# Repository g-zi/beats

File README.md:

# BEATS
## Beat Couter, MIDI controller and DMX light controller in one

A small box that is connected to the computer via USB and shows the beat as a clock and digits so that can be mixed in the beat. It can be used as a MIDI and DMX controller and can control a lighting system in the beat.

The Beat Counter knows 3 operating modes:

- MIDI (drum pad, beat clock and metronome)
- Scanners (and moving heads with up to 8 scanners with 8 channels or 4 scanners with up to 16 channels)
- COB (Pixbar and Pattern)

Can operate with anything that sends/receives MIDI commands: Ableton Live, Serato, Traktor …

Beat length adjustable, inclined beats such as 9 are also adjustable.
The key matrix is pressure-sensitive and illuminated with RGB LEDs. A milky silicone pad is attached to the key matrix.
There are two illuminated encoders that are used to set the lighting system and can also send MIDI signals.
Reads and writes MIDI signals via USB and DIN socket.
Outputs DMX control signals for light control for COB bars, 8x8 COB arrays and scanners / moving heads. Up to 8 scanners / moving heads can be controlled at the same time.
SD card slot accessible from the rear.
The housing is designed with OpenSCAD and is printed with 3D printers (Form3 or FDM)
The current version uses a Teensy 3.6, the next version will have a Teensy 4.1 (600Mhz).
The board is two-sided and created with Eagle.

Here some videos: 
- Controlling scanners / moving heads: https://www.youtube.com/watch?v=9kyjajE7mRk
- Animation of the circuit board: https://www.youtube.com/watch?v=K_6d6vQXQpI 
- Inner workings with a few functions: https://www.youtube.com/watch?v=Ms0J2bLOR1w 
- 4 x Showtec Pixel Square 16 COB (old version): https://www.youtube.com/watch?v=BX3hZSje4Ws
- Also works with bars (old version): https://www.youtube.com/watch?v=ibh8aw3B2aw
- MIDI Beat Counter Setup and Menues Part 1: https://www.youtube.com/watch?v=dCm0thBqy6s
- MIDI Beat Counter Setup and Menues Part 2: https://www.youtube.com/watch?v=OodJnmjo3fk

In MIDI mode, the key matrix is used as pressure-sensitive pads for e.g. Ableton Live. All buttons send MIDI commands. The two encoders send MIDI commands for buttons and each can be switched between 3 settings. MIDI channel and address can be set.

The scanner mode is used to control up to 8 scanners or moving heads with 8 channels or 4 scanners with up to 16 channels. All settings such as pan, tilt, color, strobe etc. can be set individually for each scanner and up to 32 settings can be saved by now.

In movement mode there are 9 movement patterns such as Left-Right, Circle, Swing etc. which the scanner let move to the rhythm of the music. The movement path and speed can be selected, in beat in steps and free run mode.

The COB mode is for COB-LED walls, until now for a matrix of 8x8 COBs. A counting pattern can be set or programmed patterns can be send out. The patterns run to the beat of the music, foreground and background brightness can be adjusted. Lightbulbs are simulated, slowly decay.

The housing is designed to be as stable as possible. On the underside there are bars under the key matrix so that nothing can bend or break even with firm pressure. The two screws for the circuit board are in the immediate vicinity of the encoder, even here nothing can be broken by applying too much pressure to the encoder. An M8 nut will also be integrated into the housing on the underside so that the device can also be screwed on. The size of the Beat Counter is kept compact and can therefore be mounted within sight.

## Further development:

The USB host port can be used to connect external devices, keyboard, drum pads etc. (Korg, Akai) https://www.pjrc.com/wp-content/uploads/2020/05/teensy41_usbhost3.jpg https://forum.pjrc.com/teensy41_usbhost2.jpg

Explanation to DMX: https://en.wikipedia.org/wiki/DMX512#RJ-45_pinout

In the current device I am using a Teensy 3.6. I am developing a circuit board for the Teensy 4.1. Teensy 4.1: https://www.pjrc.com/store/teensy41.html

Instead of the MIDI-DIN socket, an RJ45 socket will be installed: Ethernet can be used to beat-link CDJs such as beat-link-trigger or for Art-Net

Art-Net: https://artisticlicence.com/WebSiteMaster/User%20Guides/art-net.pdf

Conversion of the pattern for the COB-LED walls to the SD card and writing the program for generating the pattern, then larger output than 8x8 are possible.

Teensy 4.1 can use S/PDIF and can be later used for sound analysis, Fourier transformation and as an effects device: https://en.wikipedia.org/wiki/S/PDIF

The displays are also available in round. This display can be exchanged 1: 1 (same driver ST7789): 250nits: http://www.panelook.com/TVT0128A-I-IPS-1-28-Inch-240x240-Round-TFT-LCD-Circular-Display-Module-For-VR-detail_71679.html 400nits: http://www.panelook.com/TVT0128C-I-IPS-1-28-Inch-240x240-Round-TFT-LCD-Circular-Display-Module-For-VR-detail_98507.html or as OLED with 400x400 resolution, but are quite expensive and probably too slow: https://www.ebay.de/itm/Real-AMOLED-Display-1-39-inch-400-400-Round-Circle-Circular-OLED-LCD-Module/192716558403?var=492858328484

An LED strip control can also be installed, the neopixels are already controlled like this: https://www.ebay.de/itm/WS2812B-LED-Streifen-Strip-5M-WS2812-RGB-Leiste-Licht-5050-SMD-Adressbaren-DC5V/222192610445?hash=item33bbb62c8dⓂ️m48DHbcLw8Ppkncw-fkDSGA

Something else interesting could easily be integrated: https://github.com/saikoLED/TeensyLED

If someone is interrested to build it, I still have some PCB's and can send for 10 Euros each plus shipping costs. For further questions send email to g.zi@gmx.de

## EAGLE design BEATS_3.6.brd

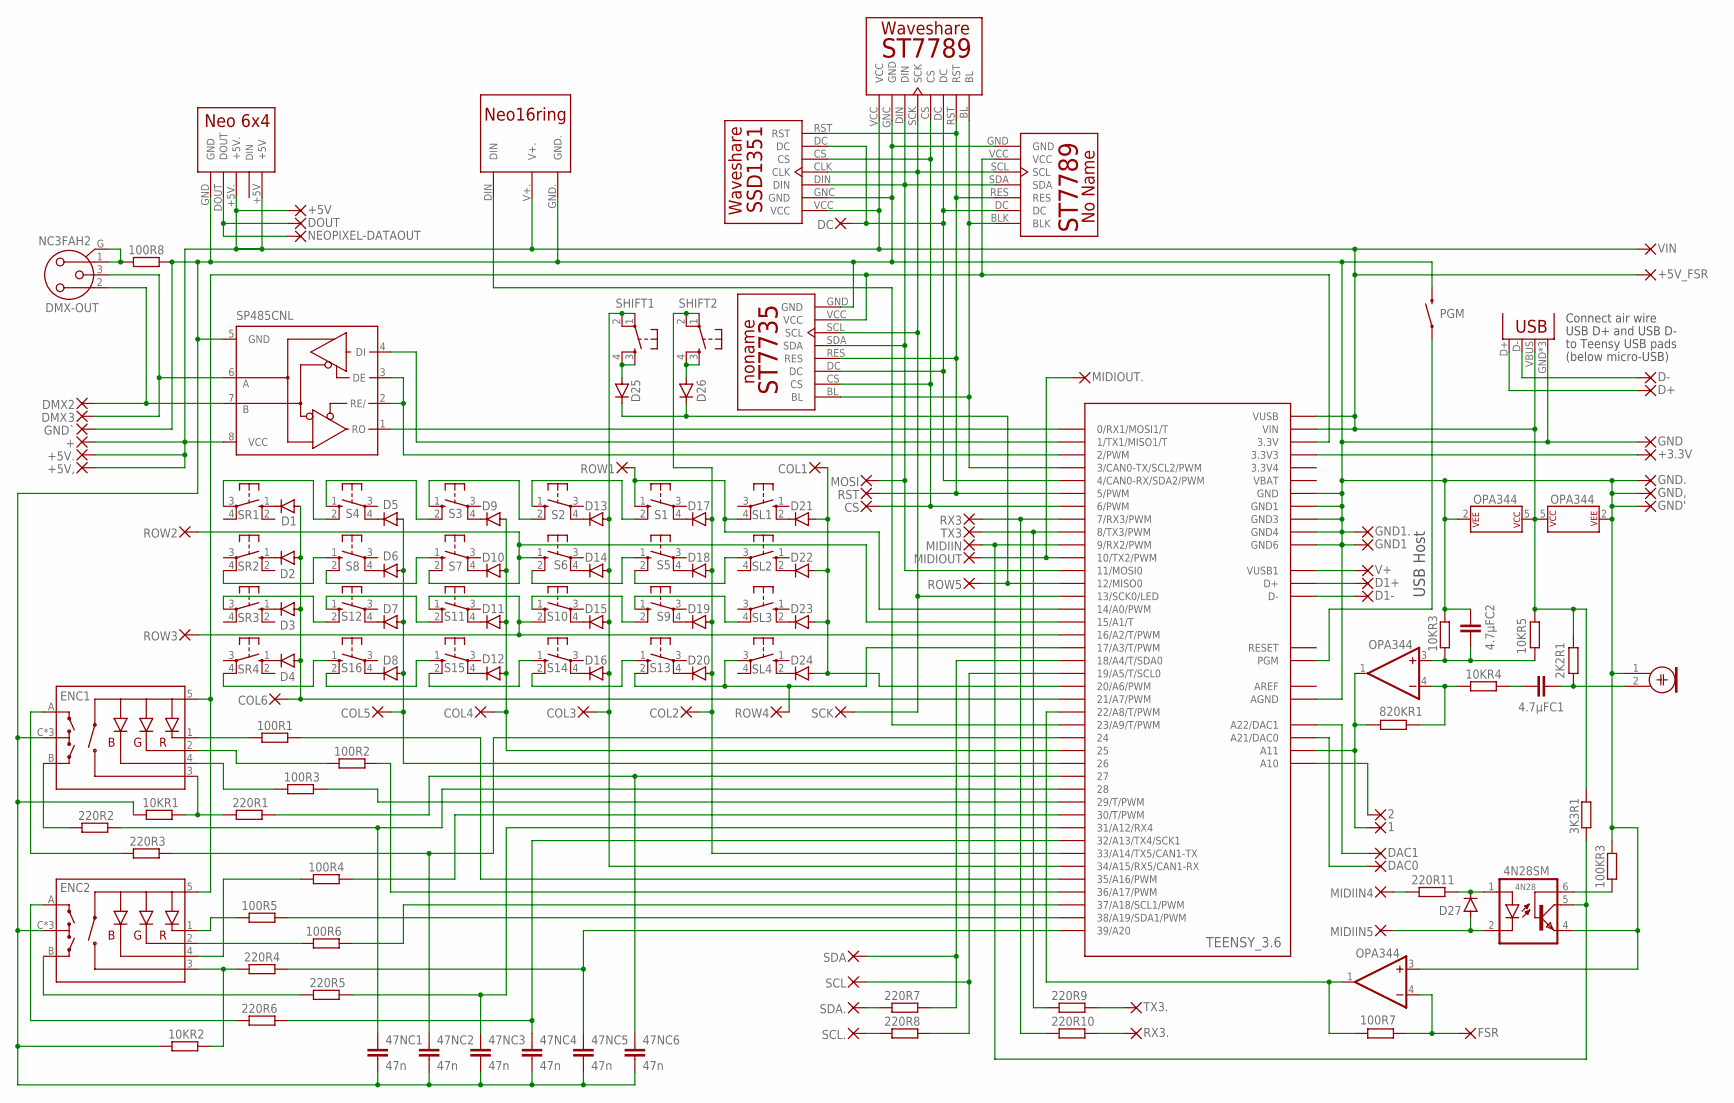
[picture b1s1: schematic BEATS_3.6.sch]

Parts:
1, 2, 3: 1,6/0,8
2K2R1: 2K2; R0603
3K3R1: 3k3; R0603
4.7µFC1, 4.7µFC2: 4.7µF; C1210
4N28: 4N28SM; DIL6-SMD
10KR1, 10KR2: 10k; R0603
10KR3, 10KR4, 10KR5: 10K; R0603
47NC1, 47NC2, 47NC3, 47NC4, 47NC5, 47NC6: 47n; C0603
100KR3: 100k; R0603
100R1, 100R2, 100R3, 100R4, 100R5, 100R6, 100R8, 220R1, 220R2, 220R3, 220R4, 220R5, 220R6, 220R7, 220R8, 220R9, 220R10, 220R11: 220R; R0603
100R7: 100R; R0603
820KR1: 820K; R0603
+, +5V, +5V,, +5V., +5V_FSR: 1,6/0,8
+3.3V: +3.3v; 1,6/0,8
COL1, COL2, COL3, COL4, COL5, COL6: 1,6/0,8
CS: 1,6/0,8
D1, D2, D3, D4, D5, D6, D7, D8, D9, D10, D11, D12, D13, D14, D15, D16, D17, D18, D19, D20, D21, D22, D23, D24, D25, D26, D27: 1N4148DO34-5; DO34-5
D1+, D1-: 1,6/0,8
D+: 1,6/0,8
D-: 1,6/0,8
DAC0, DAC1: 1,6/0,8
DC: 1,6/0,8
DMX2: 1,6/0,8
DMX-OUT: NC3FAH2
DOUT: 1,6/0,8
ENC1, ENC2: ENCODER-RGB-SWITCHENCODER_LED_3_LONG; ENCODER_LED_3_LONG
FSR: 1,6/0,8
GND, GND1, GND1., GND.: 1,6/0,8
GND': 1,6/0,8
GND,: 1,6/0,8
GND`: 1,6/0,8
MIC: ELECTRET_MICROPHON-F6035AP; F6035AP
MIDIIN, MIDIIN4, MIDIIN5: 1,6/0,8
MIDIOUT, MIDIOUT.: 1,6/0,8
MOSI: 1,6/0,8
NEOPIXEL-DATAOUT: 1,6/0,8
OPA348,, OPA348.: OPA344; SOT23-5
PGM: MOMENTARY-SWITCH-SPST-SMD-4.6X2.8MM; TACTILE_SWITCH_SMD_4.6X2.8MM
ROW1, ROW2, ROW3, ROW4, ROW5: 1,6/0,8
RST: 1,6/0,8
RX3, RX3.: 1,6/0,8
S1, S2, S3, S4, S5, S6, S7, S8, S9, S10, S11, S12, S13, S14, S15, S16: 10-XXLONG; B3F-10XX
SCK: 1,6/0,8
SCL, SCL.: 1,6/0,8
SDA, SDA.: 1,6/0,8
SHIFT1, SHIFT2: MOMENTARY-SWITCH-SPST-2-SMD-5.2MM; TACTILE_SWITCH_SMD_5.2MM
SL1, SL2, SL3, SL4: 10-XXIN; B3F-10XX1
SP485CNL: MAX3468CSA; SO08
SR1, SR2, SR3, SR4: 10-XXIN; B3F-10XX1
TEENSY_3.6: TEENSY_3.6_ALL_PINS
TX3, TX3.: 1,6/0,8
U$1: WS_1.3"240X240_3.3V
U$2: WS_1.5"128X128_OLEDOLED; WS_1.5"128X128_OLED
U$3: WS_1.3"240X240ROUND; WS_1.3"240X240_ROUND
U$4: NEO16RING
U$5: WS_1.44"128X128WS_1.44"128X128; WS_1.44"128X128
U$7: NEOPIXEL_6X4
USB-B: USB-B-H
V+: 1,6/0,8
VIN: +3.3v; 1,6/0,8

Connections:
3.3V: +3.3V.1, TEENSY_3.6.3.3V3
3.3V4: TEENSY_3.6.3.3V4
3V3: ENC1.5 (+), ENC2.5 (+), TEENSY_3.6.3.3V, U$1.VCC, U$5.VCC
AIN1: 1.1, 820KR1.1, OPA348..1 (OUT), TEENSY_3.6.A11
AIN2: 2.1, TEENSY_3.6.A10
AREF: TEENSY_3.6.AREF
BL: TEENSY_3.6.3 (3/CAN0-TX/SCL2/PWM), U$1.BLK, U$3.BL, U$5.BL
COL1: COL1.1, D21.A, D22.A, D23.A, D24.A, TEENSY_3.6.20/A6 (20/A6/PWM)
COL2: COL2.1, D17.A, D18.A, D19.A, D20.A, SHIFT2.1, SHIFT2.2, TEENSY_3.6.33/A14 (33/A14/TX5/CAN1-TX)
COL3: COL3.1, D13.A, D14.A, D15.A, D16.A, SHIFT1.1, SHIFT1.2, TEENSY_3.6.34/A15 (34/A15/RX5/CAN1-RX)
COL4: COL4.1, D9.A, D10.A, D11.A, D12.A, TEENSY_3.6.25
COL5: COL5.1, D5.A, D6.A, D7.A, D8.A, TEENSY_3.6.26
COL6: COL6.1, D1.A, D2.A, D3.A, D4.A, TEENSY_3.6.21/A7 (21/A7/PWM)
CS: CS.1, TEENSY_3.6.6 (6/PWM), U$2.CS, U$3.CS, U$5.CS
D1+: D1+.1, TEENSY_3.6.D+
D1-: D1-.1, TEENSY_3.6.D-
D+: D+.1, USB-B.D+
D-: D-.1, USB-B.D-
DAC0: DAC0.1, TEENSY_3.6.A21 (A21/DAC0)
DAC1: DAC1.1, TEENSY_3.6.A22 (A22/DAC1)
DC: DC.1, TEENSY_3.6.4 (4/CAN0-RX/SDA2/PWM), U$1.DC, U$2.DC, U$3.DC, U$5.DC
DIN: MOSI.1, TEENSY_3.6.11 (11/MOSI0), U$1.SDA, U$2.DIN, U$3.DIN, U$5.SDA
DMXEN: SP485CNL.2 (RE/), SP485CNL.3 (DE), TEENSY_3.6.2 (2/PWM)
DMXIN: SP485CNL.1 (RO), TEENSY_3.6.0 (0/RX1/MOSI1/T)
DMXIN.: DMX2.1, DMX-OUT.2 (1), SP485CNL.7 (B)
DMXOUT: SP485CNL.4 (DI), TEENSY_3.6.1 (1/TX1/MISO1/T)
DMXOUT.: 3.1, DMX-OUT.3, SP485CNL.6 (A)
DOUT: DOUT.1, NEOPIXEL-DATAOUT.1, U$7.DOUT
ENC1A: 47NC2.1, 220R3.2, TEENSY_3.6.24
ENC1A.: 220R3.1, ENC1.A
ENC1B: 47NC1.1, 220R2.2, TEENSY_3.6.28
ENC1B.: 220R2.1, ENC1.B
ENC1BL: 100R3.2, TEENSY_3.6.29 (29/T/PWM)
ENC1BL.: 100R3.1, ENC1.4 (-B)
ENC1GN: 100R2.2, TEENSY_3.6.36/A17 (36/A17/PWM)
ENC1GN.: 100R2.1, ENC1.2 (-G)
ENC1RT: 100R1.2, TEENSY_3.6.35/A16 (35/A16/PWM)
ENC1RT.: 100R1.1, ENC1.1 (-R)
ENC1SW: 47NC6.1, 220R1.2, TEENSY_3.6.27
ENC1SW.: 10KR1.2, 220R1.1, ENC1.3 (SW)
ENC2A: 47NC4.1, 220R6.2, TEENSY_3.6.32/A13 (32/A13/TX4/SCK1)
ENC2A.: 220R6.1, ENC2.A
ENC2B: 47NC3.1, 220R5.2, TEENSY_3.6.31/A12 (31/A12/RX4)
ENC2B.: 220R5.1, ENC2.B
ENC2BL: 100R4.2, TEENSY_3.6.30 (30/T/PWM)
ENC2BL.: 100R4.1, ENC2.4 (-B)
ENC2GN: 100R6.2, TEENSY_3.6.37/A18 (37/A18/SCL1/PWM)
ENC2GN.: 100R6.1, ENC2.2 (-G)
ENC2RT: 100R5.2, TEENSY_3.6.38/A19 (38/A19/SDA1/PWM)
ENC2RT.: 100R5.1, ENC2.1 (-R)
ENC2SW: 47NC5.1, 220R4.2, TEENSY_3.6.39/A20
ENC2SW.: 10KR2.2, 220R4.1, ENC2.3 (SW)
FSR: 100R7.1, OPA348,.1 (OUT), TEENSY_3.6.22/A8 (22/A8/T/PWM)
GND.: 4.7µFC2.1, 4N28.4 (EMI), 10KR1.1, 10KR2.1, 10KR3.2, 47NC1.2, 47NC2.2, 47NC3.2, 47NC4.2, 47NC5.2, 47NC6.2, 100KR3.2, 100R8.2, ENC1.C, ENC1.M1 (C), ENC1.M2 (C), ENC2.C, ENC2.M1 (C), ENC2.M2 (C), GND.1, GND1.1, GND1..1, GND'.1, GND,.1, GND..1, GND`.1, MIC.1, OPA348,.2 (P$V-), OPA348,.3 (+IN), OPA348..2 (P$V-), PGM.3 (2), PGM.4 (2), SP485CNL.5 (GND), TEENSY_3.6.AGND, TEENSY_3.6.GND, TEENSY_3.6.GND1, TEENSY_3.6.GND3, TEENSY_3.6.GND4, TEENSY_3.6.GND6, U$1.GND, U$2.GNC (GND), U$3.GNC (GND), U$4.GND., U$5.GND, U$7.GND, USB-B.GND, USB-B.P$1 (GND), USB-B.P$2 (GND)
MIC: 2K2R1.1, 4.7µFC1.2, MIC.2
MIDIIN: 3K3R1.2, 4N28.5 (COL), MIDIIN.1, TEENSY_3.6.9 (9/RX2/PWM)
MIDIIN.: 4N28.2 (C), D27.A, MIDIIN5.1
MIDIINGND: 4N28.1 (A), 220R11.2, D27.C
MIDIOUT: MIDIOUT.1, MIDIOUT..1, TEENSY_3.6.10 (10/TX2/PWM)
MISO: D25.C, D26.C, ROW5.1, TEENSY_3.6.12 (12/MISO0)
unnamed: 100R8.1, DMX-OUT.1 (2), DMX-OUT.G
unnamed: D1.C, SR1.1 (S)
unnamed: D2.C, SR2.1 (S)
unnamed: D3.C, SR3.1 (S)
unnamed: 100R7.2, FSR.1, OPA348,.4 (-IN)
unnamed: D4.C, SR4.1 (S)
unnamed: D5.C, S4.4 (P1)
unnamed: D6.C, S8.4 (P1)
unnamed: D7.C, S12.4 (P1)
unnamed: D8.C, S16.4 (P1)
unnamed: D9.C, S3.4 (P1)
unnamed: D10.C, S7.4 (P1)
unnamed: D11.C, S11.4 (P1)
unnamed: D12.C, S15.4 (P1)
unnamed: D13.C, S2.4 (P1)
unnamed: D14.C, S6.4 (P1)
unnamed: D15.C, S10.4 (P1)
unnamed: D16.C, S14.4 (P1)
unnamed: D17.C, S1.4 (P1)
unnamed: D18.C, S5.4 (P1)
unnamed: D19.C, S9.4 (P1)
unnamed: D20.C, S13.4 (P1)
unnamed: D21.C, SL1.2 (S1)
unnamed: D22.C, SL2.2 (S1)
unnamed: D23.C, SL3.2 (S1)
unnamed: D24.C, SL4.2 (S1)
unnamed: 4N28.6 (BAS), 100KR3.1
unnamed: 220R11.1, MIDIIN4.1
unnamed: D26.A, SHIFT2.3, SHIFT2.4
unnamed: D25.A, SHIFT1.3, SHIFT1.4
unnamed: 10KR4.1, 820KR1.2, OPA348..4 (-IN)
unnamed: 4.7µFC1.1, 10KR4.2
unnamed: 4.7µFC2.2, 10KR3.1, 10KR5.1, OPA348..3 (+IN)
NEO: TEENSY_3.6.23/A9 (23/A9/T/PWM), U$4.DIN
PGM: PGM.1, PGM.2 (1), TEENSY_3.6.PGM
ROW1: ROW1.1, S1.1 (S), SL1.4 (P1), TEENSY_3.6.14/A0 (14/A0/PWM)
ROW1': S3.2 (S1), S4.1 (S)
ROW1,: S2.2 (S1), S3.1 (S)
ROW1.: S1.2 (S1), S2.1 (S)
ROW1`: S4.2 (S1), SR1.3
ROW2: S5.2 (S1), SL2.3
ROW2': S7.1 (S), S8.2 (S1)
ROW2,: ROW2.1, S6.1 (S), S7.2 (S1), TEENSY_3.6.15/A1 (15/A1/T)
ROW2.: S5.1 (S), S6.2 (S1)
ROW2`: S8.1 (S), SR2.4 (P1)
ROW3: S9.1 (S), SL3.4 (P1)
ROW3': S11.2 (S1), S12.1 (S)
ROW3,: ROW3.1, S10.2 (S1), S11.1 (S), TEENSY_3.6.16/A2 (16/A2/T/PWM)
ROW3.: S9.2 (S1), S10.1 (S)
ROW3`: S12.2 (S1), SR3.3
ROW4: ROW4.1, S13.2 (S1), SL4.3, TEENSY_3.6.17/A3 (17/A3/T/PWM)
ROW4': S15.1 (S), S16.2 (S1)
ROW4,: S14.1 (S), S15.2 (S1)
ROW4.: S13.1 (S), S14.2 (S1)
ROW4`: S16.1 (S), SR4.4 (P1)
RST: RST.1, TEENSY_3.6.5 (5/PWM), U$1.RES, U$2.RST, U$3.RST, U$5.RES
RX3: 220R10.1, RX3.1, TEENSY_3.6.7 (7/RX3/PWM)
RX3.: 220R10.2, RX3..1
SCK: SCK.1, TEENSY_3.6.13 (13/SCK0/LED), U$1.SCL, U$2.CLK, U$3.SCK, U$5.SCL
SCL: 220R8.2, SCL.1, TEENSY_3.6.19/A5 (19/A5/T/SCL0)
SCL.: 220R8.1, SCL..1
SDA: 220R7.2, SDA.1, TEENSY_3.6.18/A4 (18/A4/T/SDA0)
SDA.: 220R7.1, SDA..1
TX3: 220R9.1, TEENSY_3.6.8 (8/TX3/PWM), TX3.1
TX3.: 220R9.2, TX3..1
V1: TEENSY_3.6.VUSB1, V+.1
VBAT: TEENSY_3.6.VBAT
VUSB: 2K2R1.2, 3K3R1.1, 10KR5.2, +.1, +5V.1, +5V,.1, +5V..1, +5V_FSR.1, OPA348,.5 (P$V+), OPA348..5 (P$V+), SP485CNL.8 (VCC), TEENSY_3.6.VIN, TEENSY_3.6.VUSB, U$2.VCC, U$3.VCC, U$4.V+., U$7.+5V, U$7.+5V., USB-B.VBUS, VIN.1

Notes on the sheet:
USB Host
USB D+ and USB D-
Connect air wire
to Teensy USB pads
(below micro-USB)
DMX

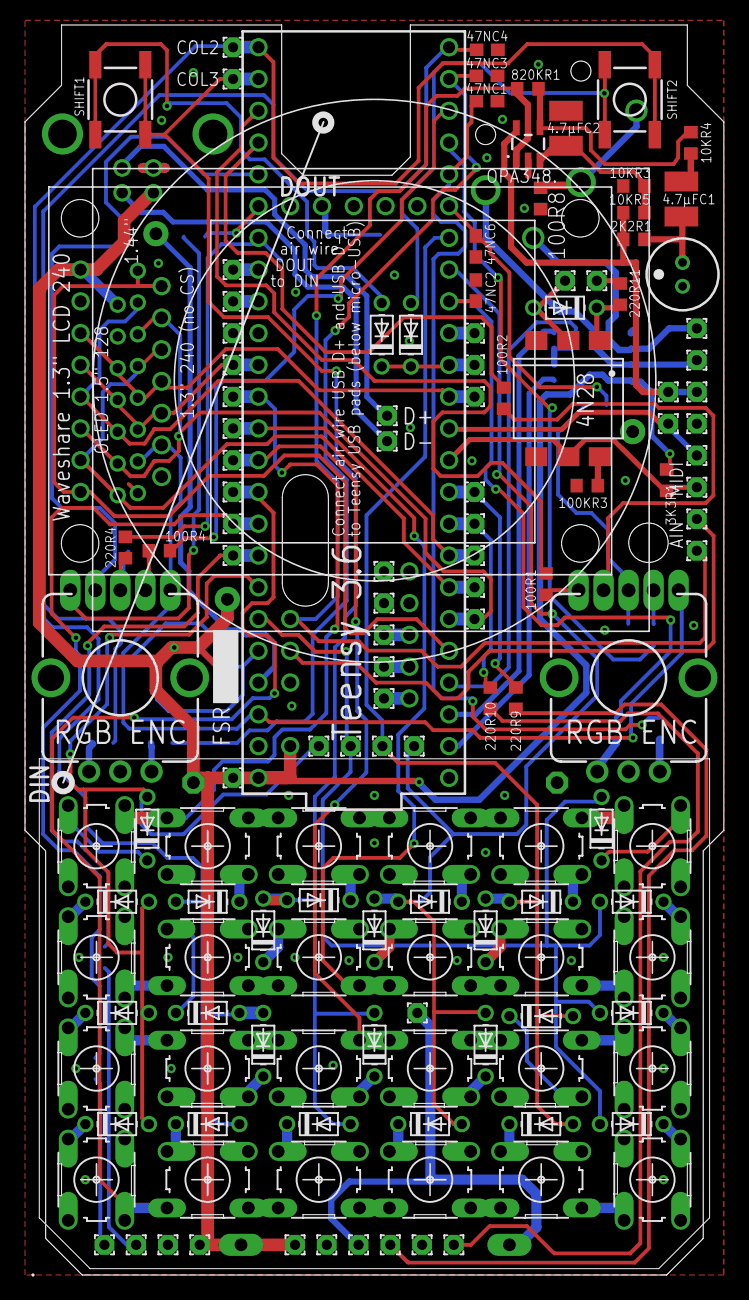
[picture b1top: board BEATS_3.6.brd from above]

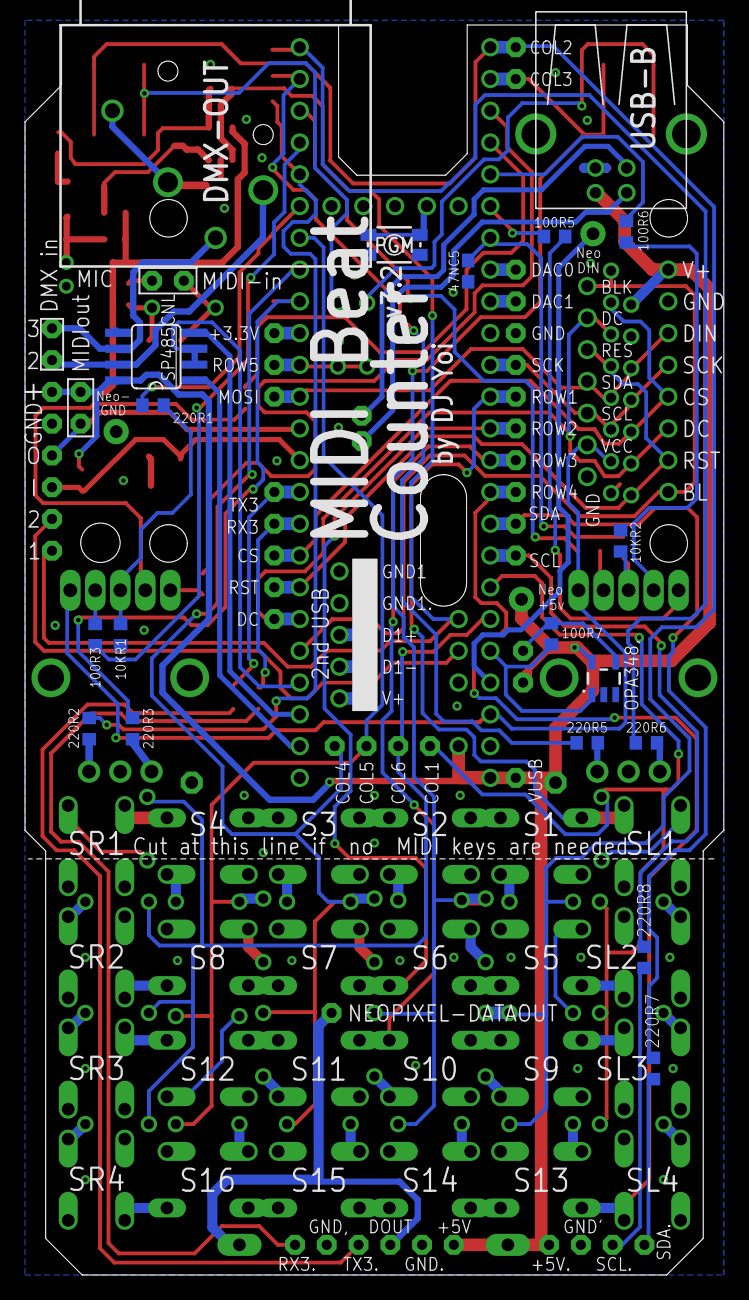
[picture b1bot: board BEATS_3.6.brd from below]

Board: 2 copper layers, 55.9 x 99.9 mm, 163 parts (19 on the bottom side), 125 nets.

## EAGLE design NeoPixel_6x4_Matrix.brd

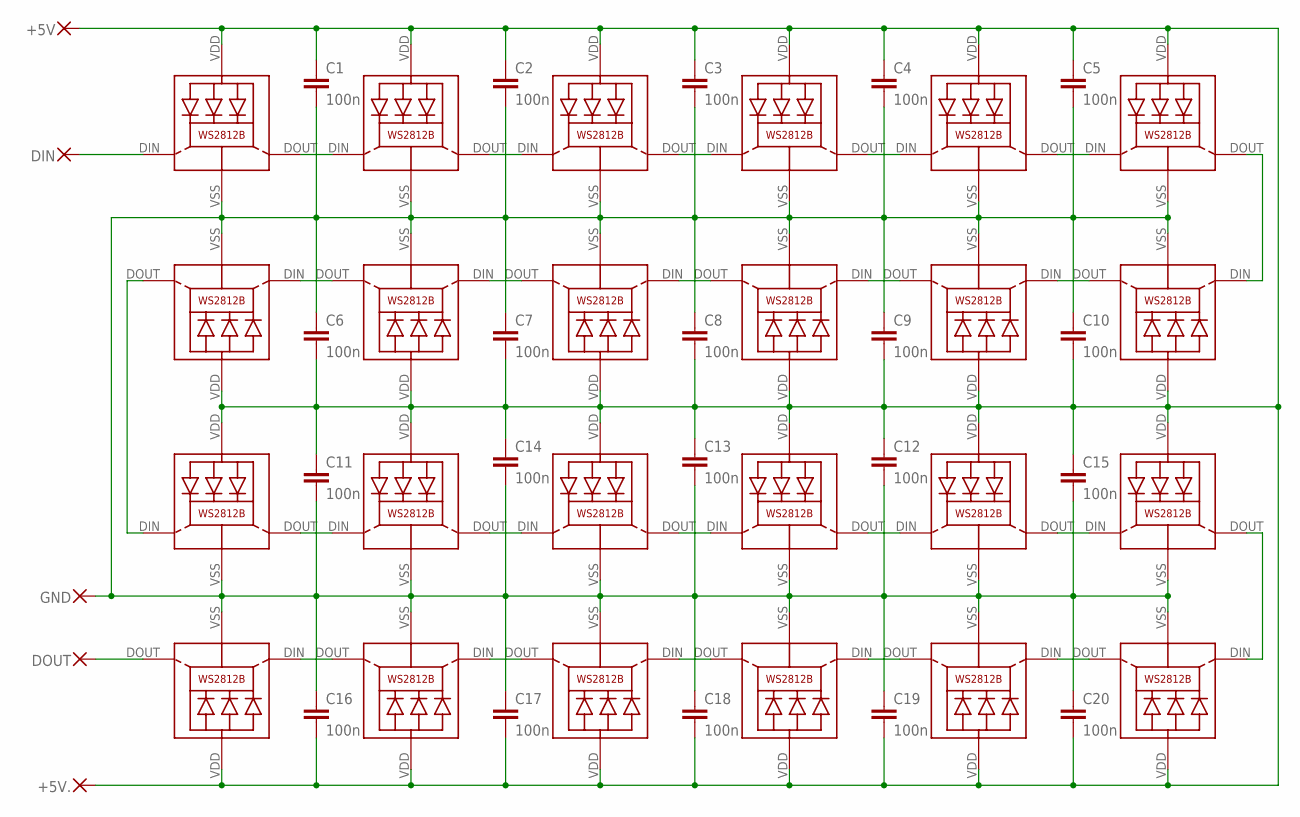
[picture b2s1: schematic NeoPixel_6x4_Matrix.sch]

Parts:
+5V, +5V.: 1,6/0,8
C1, C2, C3, C4, C5, C6, C7, C8, C9, C10, C11, C12, C13, C14, C15, C16, C17, C18, C19, C20: 100n; C0603
DIN: 1,6/0,8
DOUT: 1,6/0,8
GND: 1,6/0,8
LED1, LED2, LED3, LED4, LED5, LED6, LED7, LED8, LED9, LED10, LED11, LED12, LED13, LED14, LED15, LED16, LED17, LED18, LED19, LED20, LED21, LED22, LED23, LED24: WS2812B

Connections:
1-2: LED2.DOUT (DO), LED3.DIN (DI)
2-3: LED3.DOUT (DO), LED4.DIN (DI)
3-4: LED4.DOUT (DO), LED5.DIN (DI)
4-5: LED6.DOUT (DO), LED7.DIN (DI)
5-6: LED8.DOUT (DO), LED9.DIN (DI)
6-7: LED9.DOUT (DO), LED10.DIN (DI)
7-8: LED10.DOUT (DO), LED11.DIN (DI)
8-9: LED12.DOUT (DO), LED13.DIN (DI)
9-10: LED14.DOUT (DO), LED15.DIN (DI)
10-11: LED15.DOUT (DO), LED16.DIN (DI)
11-12: LED16.DOUT (DO), LED17.DIN (DI)
12-13: LED18.DOUT (DO), LED19.DIN (DI)
13-14: LED20.DOUT (DO), LED21.DIN (DI)
14-15: LED21.DOUT (DO), LED22.DIN (DI)
15-16: LED22.DOUT (DO), LED23.DIN (DI)
unnamed: LED1.DOUT (DO), LED2.DIN (DI)
unnamed: DIN.1, LED1.DIN (DI)
unnamed: LED5.DOUT (DO), LED6.DIN (DI)
unnamed: LED7.DOUT (DO), LED8.DIN (DI)
unnamed: DOUT.1, LED24.DOUT (DO)
unnamed: LED17.DOUT (DO), LED18.DIN (DI)
unnamed: LED11.DOUT (DO), LED12.DIN (DI)
unnamed: LED13.DOUT (DO), LED14.DIN (DI)
unnamed: LED23.DOUT (DO), LED24.DIN (DI)
unnamed: LED19.DOUT (DO), LED20.DIN (DI)
VDD: +5V.1, +5V..1, C1.1, C2.1, C3.1, C4.1, C5.1, C6.2, C7.2, C8.2, C9.2, C10.2, C11.1, C12.1, C13.1, C14.1, C15.1, C16.2, C17.2, C18.2, C19.2, C20.2, LED1.VDD, LED2.VDD, LED3.VDD, LED4.VDD, LED5.VDD, LED6.VDD, LED7.VDD, LED8.VDD, LED9.VDD, LED10.VDD, LED11.VDD, LED12.VDD, LED13.VDD, LED14.VDD, LED15.VDD, LED16.VDD, LED17.VDD, LED18.VDD, LED19.VDD, LED20.VDD, LED21.VDD, LED22.VDD, LED23.VDD, LED24.VDD
VSS: C1.2, C2.2, C3.2, C4.2, C5.2, C6.1, C7.1, C8.1, C9.1, C10.1, C11.2, C12.2, C13.2, C14.2, C15.2, C16.1, C17.1, C18.1, C19.1, C20.1, GND.1, LED1.VSS (GND), LED2.VSS (GND), LED3.VSS (GND), LED4.VSS (GND), LED5.VSS (GND), LED6.VSS (GND), LED7.VSS (GND), LED8.VSS (GND), LED9.VSS (GND), LED10.VSS (GND), LED11.VSS (GND), LED12.VSS (GND), LED13.VSS (GND), LED14.VSS (GND), LED15.VSS (GND), LED16.VSS (GND), LED17.VSS (GND), LED18.VSS (GND), LED19.VSS (GND), LED20.VSS (GND), LED21.VSS (GND), LED22.VSS (GND), LED23.VSS (GND), LED24.VSS (GND)

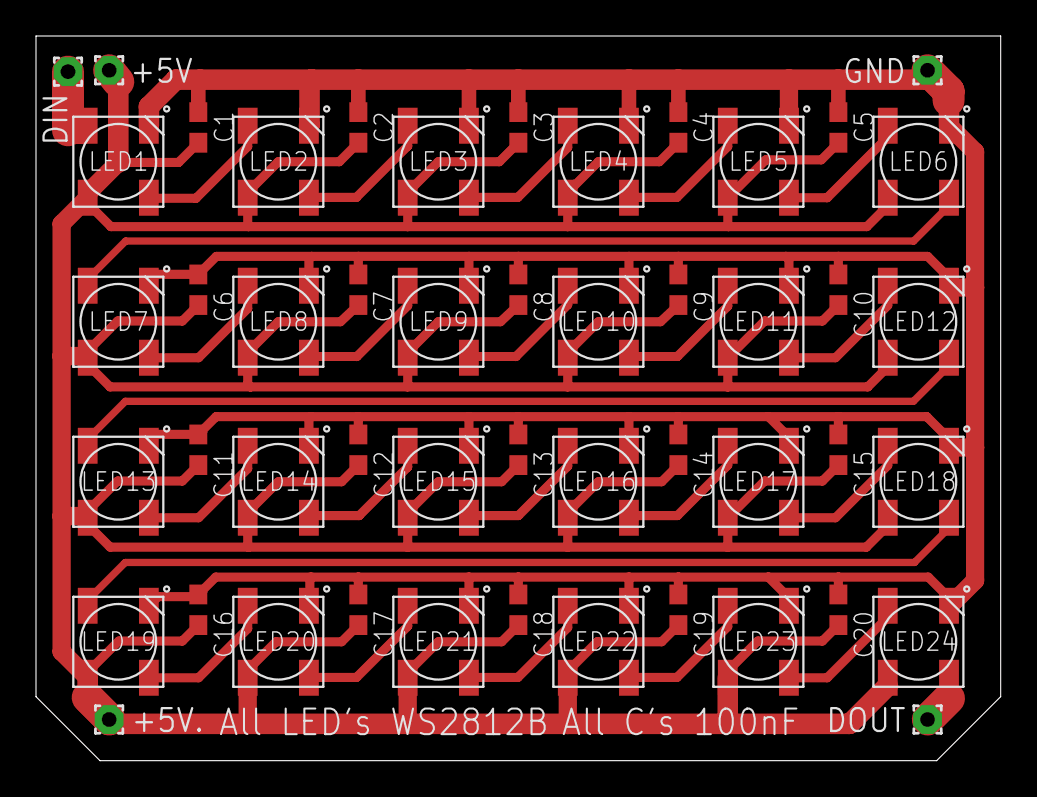
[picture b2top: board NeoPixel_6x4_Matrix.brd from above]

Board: 2 copper layers, 53.6 x 40.3 mm, 49 parts (0 on the bottom side), 27 nets.

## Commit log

2021-12-25 Bom update

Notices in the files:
parts and their libraries:
SparkFun-Switches: Licensing: Creative Commons ShareAlike 4.0 International - https://creativecommons.org/licenses/by-sa/4.0
